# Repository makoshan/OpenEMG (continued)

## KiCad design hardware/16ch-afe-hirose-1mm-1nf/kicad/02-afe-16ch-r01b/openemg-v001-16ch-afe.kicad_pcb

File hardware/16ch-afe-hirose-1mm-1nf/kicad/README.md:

# OpenEMG v0.01（16CH 双板 + 九页原理图）— KiCad 8 原生工程

本目录由同级 [`../OpenEMG_v0.01_DualBoard.epro2`](../OpenEMG_v0.01_DualBoard.epro2)（`OpenEMG_v0.01_双板工程_九页原理图_20261115.epro2`）1:1 转换生成，完整保留双板封装焊盘、过孔、铜线、铺铜区域（`zone`）、可见位号丝印（遵循 `.epru` `Designator.valueVisible`）、`LM1` 散热焊盘双窗钢网分割（`78.2%`），以及全部 9 页原理图与立创 `LCSC` / `MPN` 属性。可直接用 **KiCad 8.0+** 或 **Backplane GPUI** 打开查看与联调。

## 目录结构

| 子目录 | 包含文件 | 对应源工程与说明 |
| :--- | :--- | :--- |
| [`02-afe-16ch-r01b/`](02-afe-16ch-r01b/) | `openemg-v001-16ch-afe.kicad_pro`<br>`openemg-v001-16ch-afe.kicad_pcb`<br>`openemg-v001-16ch-afe.kicad_sch` | **`02 采集板（AFE-16CH，R01b）`**：`43.10 × 36.50 mm` 四角 `R1.80` 4 层板（150 器件 = 146 贴片 + 4 定位孔、2239 段铜线、234 过孔、14 铜皮 + `LM1` 双窗钢网）+ `02.01 / 02.02` 合并原理图 |
| [`01-mainboard-c08b-u9/`](01-mainboard-c08b-u9/) | `openemg-v001-mainboard-u9.kicad_pro`<br>`openemg-v001-mainboard-u9.kicad_pcb`<br>`openemg-v001-mainboard-u9.kicad_sch` | **`01 主控板（C08B-U9，OpenEMG）`**：`43.10 × 36.50 mm` 四角 `R1.80` 6 层板（`STM32L432KB + nRF52840`，128 器件、1114 段铜线、204 过孔、24 铜皮）+ `01.01 ~ 01.07` 合并原理图 |
| [`nine-pages-sch/`](nine-pages-sch/) | `01_01.kicad_sch` ～ `01_07.kicad_sch`<br>`02_01.kicad_sch` ～ `02_02.kicad_sch` | **9 页独立单页 KiCad 原理图**：`01.01` 整机框图、`01.02` 电源树、`01.03–01.07` 主控电路、`02.01` 双 `ADS1298R` 与模拟电源、`02.02` 双 30P 广濑接口与 32 路 `ESD401DPYR` 滤波网络 |

> **投产提示**：打板与 SMT 贴片请直接使用上级目录经人工工程师逐脚审核定版的生产制造包（[`../Gerber_AFE-30P.zip`](../Gerber_AFE-30P.zip)、[`../Gerber_C08B-U9_v0.01.zip`](../Gerber_C08B-U9_v0.01.zip)、[`../jlc_smt_bom.csv`](../jlc_smt_bom.csv)、[`../jlc_smt_cpl.csv`](../jlc_smt_cpl.csv)）。

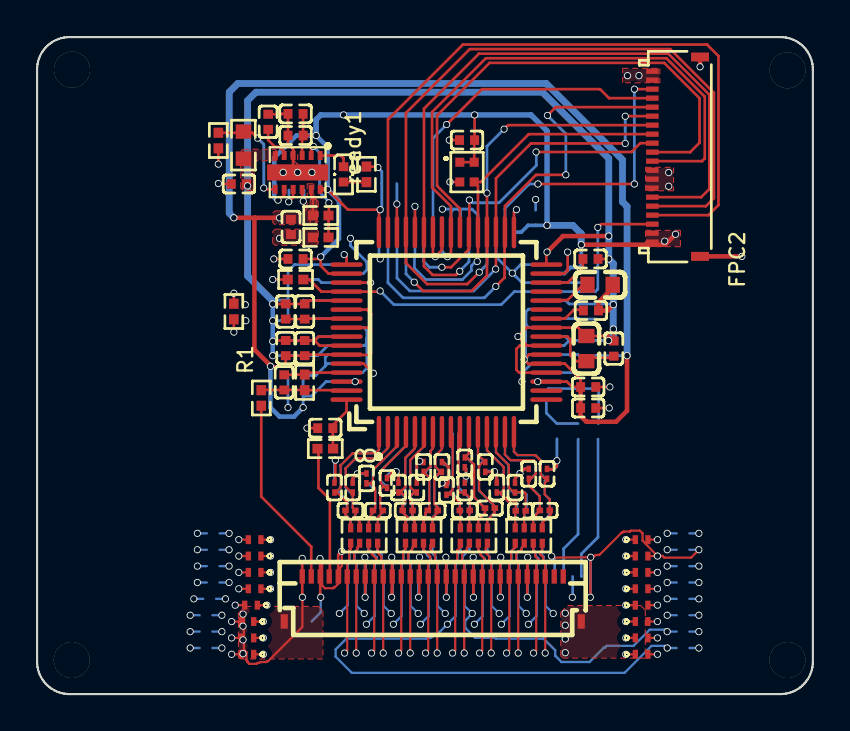
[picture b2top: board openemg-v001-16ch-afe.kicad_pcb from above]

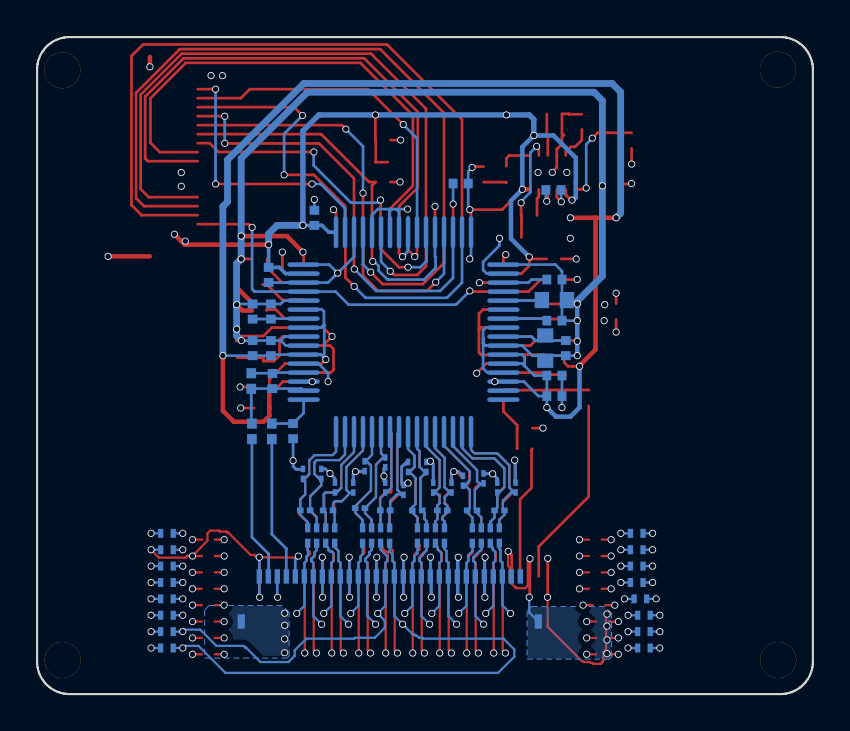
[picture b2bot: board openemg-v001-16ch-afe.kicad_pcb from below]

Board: 4 copper layers, 43.1 x 36.5 mm, 150 parts (66 on the bottom side), 109 nets.

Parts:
C1, C2: 22uF; C0603
C3, C5, C8, C18, C21, C22, C24, C26, C28, C30, C32, C37: 100nF; C0402
C4, C34: 47uF; C0603
C6, C7: 2.2uF; C0402
C9, C11: 10uF; C0402
C10, C12, C13, C15, C16, C19, C20, C23, C25, C27, C29, C31, C33: 1uF; C0402
C14, C17: 10nF; C0402
C55, C57, C58, C59, C60, C61, C62, C63, C64, C65, C66, C67, C68, C69, C70, C71, C93, C94, C95, C96, C97, C98, C99, C100, C101, C102, C103, C104, C105, C106, C107, C108: 470pF; C0201
C72, C73, C74, C75, C76, C77, C78, C79, C109, C110, C111, C112, C113, C114, C115, C116: 1nF; C0201
C123, C124: 100pF; C0402
D101, D102, D103, D104, D105, D106, D107, D108, D109, D110, D111, D112, D113, D114, D115, D116, D117, D118, D119, D120, D121, D122, D123, D124, D125, D126, D127, D128, D129, D130, D131, D132: ESD401DPYR; X1SON-2_L1.0-W0.6-P0.65-BI
FPC1, FPC3: FH34SRJ-30S-0.5SH(50); FFC-SMD_30P-P0.50_FH34SRJ-30S-0.5SH
FPC2: 5034802000; FPC-SMD_5034802000
LM1: LM27762DSSR; WSON-12_L3.0-W2.0-P0.50-BL-EP
R1: 0Ω; R0402
R3, R5: 100kΩ; R0402
R4: 104kΩ; R0603
R6: 107kΩ; R0402
R17, R35, R37: 10kΩ; R0402
R24, R32, R34, R36: 392kΩ; R0402
R_pu1: 10kΩ; R0402
SCREW1, SCREW2, SCREW3, SCREW4: M2螺丝
U1, U2: ADS1298IPAGR; TQFP-64_L10.0-W10.0-P0.50-LS12.0-BL
U3, U4, U5, U6, U7, U8, U9, U10: 15kΩ; RES-ARRAY-SMD_0402-8P-L2.0-W1.0-BL
X1: 2.048MHz; OSC-SMD_4P-L1.6-W1.2-BL
ready1: XL-1005UGC; LED0402-RD_GREEN

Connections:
$1N19: C3.2, C4.2, U1.24
$1N24: C12.1, U1.26
$1N26: C13.1, U1.30
$1N44: C20.2, C21.2, U1.55
$1N303: C16.1, U2.30
$1N305: C15.1, U2.26
$1N315: C5.2, C34.2, U2.24
$1N319: C18.2, C19.2, U2.55
$1N346: C123.1, R35.1, U1.64
$1N349: C124.1, R37.1, U2.64
$1N350: C1.1, U1.28
$1N351: C2.1, U2.28
$1N375: C11.1, LM1.5
$1N383: C10.2, LM1.9
$1N384: C10.1, LM1.10
$1N395: R_pu1.2, ready1.2
+2.5V: C6.1, C24.1, C25.1, C26.1, C27.1, C30.1, C31.1, C32.1, C33.1, LM1.11, R6.2, U1.19, U1.21, U1.22, U1.54, U1.56, U1.59, U1.62, U2.19, U2.21, U2.22, U2.54, U2.56, U2.59, U2.62
+3.3V: C8.2, C9.1, C22.1, C23.1, C28.1, C29.1, C37.2, FPC2.1, FPC2.2, LM1.3, LM1.8, LM1.12, R_pu1.1, U1.48, U1.50, U2.48, U2.50, X1.1, X1.4
-2.5V: C1.2, C2.2, C3.1, C4.1, C5.1, C7.1, C12.2, C13.2, C15.2, C16.2, C18.1, C19.1, C20.1, C21.1, C26.2, C27.2, C32.2, C33.2, C34.1, LM1.6, R4.2, U1.20, U1.23, U1.25, U1.32, U1.53, U1.57, U1.58, U2.20, U2.23, U2.25, U2.32, U2.53, U2.57, U2.58
AGND: C6.2, C7.2, C8.1, C9.2, C11.2, C24.2, C25.2, C30.2, C31.2, C55.1, C57.1, C58.1, C59.1, C60.1, C61.1, C62.1, C63.1, C64.1, C65.1, C66.1, C67.1, C68.1, C69.1, C70.1, C71.1, C93.1, C94.1, C95.1, C96.1, C97.1, C98.1, C99.1, C100.1, C101.1, C102.1, C103.1, C104.1, C105.1, C106.1, C107.1, C108.1, C123.2, C124.2, D101.2, D102.2, D103.2, D104.2, D105.2, D106.2, D107.2, D108.2, D109.2, D110.2, D111.2, D112.2, D113.2, D114.2, D115.2, D116.2, D117.2, D118.2, D119.2, D120.2, D121.2, D122.2, D123.2, D124.2, D125.2, D126.2, D127.2, D128.2, D129.2, D130.2, D131.2, D132.2, FPC1.5, FPC1.8, FPC1.11, FPC1.14, FPC1.17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
BIASINV1: C14.1, R24.1, U1.61
BIASINV12: C17.1, R32.1, U2.61
BIASOUT1: C14.2, R24.2, R34.1, U1.63
BIASOUT12: C17.2, R32.2, R36.1, U2.63
BIAS_DRV1: FPC1.29, R34.2
BIAS_DRV12: FPC3.29, R36.2
CLK: FPC2.13, U1.37, U2.37, X1.3
CLKSEL: FPC2.3, R17.2, U1.52, U2.52
CS#: FPC2.11, U1.39
CS#2: FPC2.17, U2.39
DIN: FPC2.16, U1.34, U2.34
DOUT: FPC2.6, U1.43, U2.43
DRDY2#: FPC2.18, U2.47
DRDY#: FPC2.4, U1.47
EL_CH1_N: D102.1, FPC1.4, U6.2
EL_CH1_P: D101.1, FPC1.3, U6.1
EL_CH2_N: D104.1, FPC1.7, U6.4
EL_CH2_P: D103.1, FPC1.6, U6.3
EL_CH3_N: D106.1, FPC1.10, U5.2
EL_CH3_P: D105.1, FPC1.9, U5.1
EL_CH4_N: D108.1, FPC1.13, U5.4
EL_CH4_P: D107.1, FPC1.12, U5.3
EL_CH5_N: D110.1, FPC1.16, U4.2
EL_CH5_P: D109.1, FPC1.15, U4.1
EL_CH6_N: D112.1, FPC1.19, U4.4
EL_CH6_P: D111.1, FPC1.18, U4.3
EL_CH7_N: D114.1, FPC1.22, U3.2
EL_CH7_P: D113.1, FPC1.21, U3.1
EL_CH8_N: D116.1, FPC1.25, U3.4
EL_CH8_P: D115.1, FPC1.24, U3.3
EL_CH9_N: D118.1, FPC3.4, U10.2
EL_CH9_P: D117.1, FPC3.3, U10.1
EL_CH10_N: D120.1, FPC3.7, U10.4
EL_CH10_P: D119.1, FPC3.6, U10.3
EL_CH11_N: D122.1, FPC3.10, U9.2
EL_CH11_P: D121.1, FPC3.9, U9.1
EL_CH12_N: D124.1, FPC3.13, U9.4
EL_CH12_P: D123.1, FPC3.12, U9.3
EL_CH13_N: D126.1, FPC3.16, U8.2
EL_CH13_P: D125.1, FPC3.15, U8.1
EL_CH14_N: D128.1, FPC3.19, U8.4
EL_CH14_P: D127.1, FPC3.18, U8.3
EL_CH15_N: D130.1, FPC3.22, U7.2
EL_CH15_P: D129.1, FPC3.21, U7.1
EL_CH16_N: D132.1, FPC3.25, U7.4
EL_CH16_P: D131.1, FPC3.24, U7.3
FB: LM1.2, R3.2, R6.1
FB-: LM1.7, R4.1, R5.2
GND: C22.2, C23.2, C28.2, C29.2, C37.1, FPC2.7, FPC2.8, FPC2.9, FPC2.19, FPC2.20, FPC2.21, FPC2.22, R1.2, R17.1, U1.31, U1.33, U1.41, U1.42, U1.44, U1.46, U1.49, U1.51, U2.31, U2.33, U2.41, U2.42, U2.44, U2.46, U2.49, U2.51, X1.2
GPIO3: FPC2.5, U1.45, U2.45
IN1N: C57.2, C72.1, U1.15, U6.7
IN1N2: C94.2, C109.1, U2.15, U10.7
IN1P: C55.2, C72.2, U1.16, U6.8
IN1P2: C93.2, C109.2, U2.16, U10.8
IN2N: C59.2, C73.1, U1.13, U6.5
IN2N2: C96.2, C110.1, U2.13, U10.5
IN2P: C58.2, C73.2, U1.14, U6.6
IN2P2: C95.2, C110.2, U2.14, U10.6
IN3N: C61.2, C74.1, U1.11, U5.7
IN3N2: C98.2, C111.1, U2.11, U9.7
IN3P: C60.2, C74.2, U1.12, U5.8
IN3P2: C97.2, C111.2, U2.12, U9.8
IN4N: C63.2, C75.1, U1.9, U5.5
IN4N2: C100.2, C112.1, U2.9, U9.5
IN4P: C62.2, C75.2, U1.10, U5.6
IN4P2: C99.2, C112.2, U2.10, U9.6
IN5N: C65.2, C76.1, U1.7, U4.7
IN5N2: C102.2, C113.1, U2.7, U8.7
IN5P: C64.2, C76.2, U1.8, U4.8
IN5P2: C101.2, C113.2, U2.8, U8.8
IN6N: C67.2, C77.1, U1.5, U4.5
IN6N2: C104.2, C114.1, U2.5, U8.5
IN6P: C66.2, C77.2, U1.6, U4.6
IN6P2: C103.2, C114.2, U2.6, U8.6
IN7N: C69.2, C78.1, U1.3, U3.7
IN7N2: C106.2, C115.1, U2.3, U7.7
IN7P: C68.2, C78.2, U1.4, U3.8
IN7P2: C105.2, C115.2, U2.4, U7.8
IN8N: C71.2, C79.1, U1.1, U3.5
IN8N2: C108.2, C116.1, U2.1, U7.5
IN8P: C70.2, C79.2, U1.2, U3.6
IN8P2: C107.2, C116.2, U2.2, U7.6
POWERGOOD: LM1.1, ready1.1
PWDN#: FPC2.15, U1.35, U2.35
RESET#: FPC2.14, U1.36, U2.36
SCLK: FPC2.10, U1.40, U2.40
START: FPC2.12, U1.38, U2.38
WCT: FPC1.27, R35.2
WCT2: FPC3.27, R37.2

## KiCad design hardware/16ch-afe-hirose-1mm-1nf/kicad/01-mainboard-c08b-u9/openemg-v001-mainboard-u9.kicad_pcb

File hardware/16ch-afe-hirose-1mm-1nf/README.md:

# 16 通道双板汇总工程与 1.0 mm 广濑双 30 针 1 nF 采集板（`v0.01`）

**2026-11-15 人工工程师设计并逐脚审核通过（ESD32 · 准备下单打样）。** 本目录双板（`01 主控板 C08B-U9` + `02 采集板 AFE-30P`）是当前仓库中**唯一由人工硬件工程师设计、并对照 TI `ADS1298` 手册与 `SBAU171D` 评估板指南逐脚审核通过、准备下单打样的硬件定版**；仓库内其余 2/8/16 通道衍生板、柔性电极软板与 3D 外壳均为 AI 生成且尚未下单。项目仍在早期研制，尚无本版整机台架或佩戴实测。

本目录归档 `OpenEMG v0.01` 双板合并嘉立创 EDA 专业版工程（含 6 层主控板与 4 层 16 通道采集板，共 9 页原理图 + 2 块圆角 `43.10 × 36.50 mm`、`R1.80` PCB），以及与该工程采集板逐位号同步导出的四层单板生产制造包。

| 识别项 | 本目录广濑 `1 nF` 版（`v0.01`） | [讯普 `2.0 mm` `1 nF` 版](../16ch-afe-xunpu-2mm-1nf/) | [广濑 `22 pF` 穿戴版](../16ch-u9-dual30/) |
|---|---|---|---|
| 工程形态 | 双板合并 `.epro2`（`01 主控板` + `02 采集板`） | 采集板独立 `.epro` / `.epro2` | 主控与采集板分立 `.epro2` + 软板 + 外壳 |
| 板框包络 | `43.10 × 36.50 mm`，四角 `R1.80` 圆角 | `43.10 × 36.67 mm`，直角 | `43.10 × 36.50 mm`，四角 `R1.80` 圆角 |
| `FPC1`、`FPC3` 表带座 | 广濑 `FH34SRJ-30S-0.5SH(50)`，`1.0 mm` 超薄上下双触点，`C324727` | 讯普 `FPC-05F-30PH20`，`2.0 mm`，`C2856808` | 广濑 `FH34SRJ-30S-0.5SH(50)`，`1.0 mm`，`C324727` |
| 输入 RC 网络 | `32 × 15 kΩ` + `32 × 470 pF` 对地 + `16 × 1 nF` 跨通道 | `32 × 15 kΩ` + `32 × 470 pF` 对地 + `16 × 1 nF` 跨通道 | `32 × 15 kΩ` + 32 颗共模空贴 DNP + `16 × 22 pF` 跨通道 |
| 负电源反馈 `R4` | `104 kΩ ±0.1%`（0603，`RT0603BRD07104KL`，`C861070`，现货） | `105 kΩ`（0402，`C2984407`） | `105 kΩ ±0.1%`（0402，`C2984407`） |
| 偏置串阻 `R34`、`R36` | `392 kΩ`（0402，`C27007`） | `392 kΩ`（暂选待回签） | `392 kΩ`（0402，`C99199`，配 `100 kΩ/200 kΩ` 保护软板） |

### 在线看图

[九页原理图（矢量 PDF）](views/schematic.pdf) · [主控六层走线](views/mcu-copper.png) · [采集四层走线](views/afe-copper.png) · [双板叠放](views/v001-stack-iso-dark.png) · [结构爆炸图](views/v001-exploded-iso-dark.png)

公开工程沿用 11 月 15 日的 PCB。主控五页按功能标出电源、接口、蓝牙和采样主控。采集部分按 CH1–8、CH9–16 标注芯片和滤波器，输入保护管 D101–D132 按通道顺序排列，使用 ESD401 的双向保护符号。

九页 PDF 由整机框图、电源树、主控电路五页和[从公开工程导出的采集板两页](views/afe-schematic.pdf)合并。D101–D132 分布在两面，分别保护 32 根输入线。走线图使用本目录两个 Gerber 包，按顶层、内层、底层排列，底层保持板顶视角。装配图使用相同 Gerber 的板框、阻焊和丝印，搭配 U9 壳体 CAD，按 0.8 mm 裸板展示。

### 工程与制造文件

2026-11-15 离体台架打样版已同步。两块 PCB 各删除四处安装孔的顶层圆圈和斜线，孔位、铜层、钢网和钻孔文件与上一版一致。打样以以下 Gerber、BOM 和坐标为准，上方装配渲染为改丝印前的示意。

[双板合并嘉立创工程 `.epro2`](OpenEMG_v0.01_DualBoard.epro2) · [KiCad 8 原生工程（双板 PCB + 九页原理图）](kicad/) · [采集板单板 Gerber（含钻孔与 `LM1` 双窗钢网）](Gerber_AFE-30P.zip) · [采集板贴片 BOM](jlc_smt_bom.csv) · [采集板贴片坐标 CPL](jlc_smt_cpl.csv)

- **采集板贴片清单**：整板共 **24 种料、146 个贴片位号**（顶面 80 个、底面 66 个，已剔除 4 个非贴片定位孔 `SCREW1–SCREW4`）；上传 `jlc_smt_cpl.csv` 时保持嘉立创平台默认的 **「AD,99SE,Allegro,PADS(宏)等其他」** 选项（切勿改选「嘉立创EDA」），并在贴片预览页核对 `U1/U2/FPC1–FPC3` 第 1 脚朝向。Gerber、BOM、CPL 与底面装配图成套同步，不可与直角框或 `0402 R4` 的历史文件混用。
- **配套主控板制造包**：双板工程内的 `01 主控板` 与 [`../16ch-u9-dual30/fab-mcu-u9/`](../16ch-u9-dual30/fab-mcu-u9/) 铜皮走线及 110 颗贴片位号一致（主控贴片需排除测试点、焊盘电池座 `J401` 及默认禁贴跨接件 `JP701 / R7 / R213`，本版使用[主控贴片 BOM](mainboard_bom.csv) 和[双面坐标](mainboard_cpl.csv)，本次主控打样使用[评审后主控单板 Gerber](Gerber_C08B-U9_v0.01.zip)；注：`.epro2` 源内 `J401` 原理图符号保留第 3 空置 NTC 引脚且机械定位孔勾有加入 BOM，切勿从 `.epro2` 直接一键导出 BOM/钢网投产）。

### 采集板打样与安全边界须知

- 按定版打样包选择盘中孔树脂塞孔、电镀盖帽。LM1 顶面散热焊盘的钢网已分成双窗，使用本目录 Gerber。
- 离体台架首板按 1.6 mm 板厚；U9 外壳渲染按 0.8 mm 裸板展示，装壳与排线仍需试装。
- 两颗 `ADS1298` 的 `Pin 60 (RLDREF)` 接 `AGND`、`Pin 62 (RLDIN)` 接 `+2.5 V`、`Pin 17/18 (TESTP/TESTN)` 独立悬空。[`firmware/c08b-bringup`](../../firmware/c08b-bringup/) 与 [`firmware/c08b-stream`](../../firmware/c08b-stream/) 已据此完成寄存器与网表对齐（`TST1` 下双片均置 `CONFIG2=0x10`，`CONFIG3` 强制 `(val & 0x38)==0` 禁置 `VREF_4V / RLD_MEAS / RLDREF_INT` 且禁设 `MUX=0x02`）。偏置回路、通道底噪、丢帧与佩戴安全尚待首板实测验证。[安全说明](../../SAFETY.md)

### 双面贴片方向

[顶面贴片极性图](assembly-top.png) · [底面贴片极性图](assembly-bottom.png)。红点标出第 1 脚，角度对应同版 CPL。底面图按翻到板背后的方向显示。

### 配套表带软板（A5＋B1）与 25 mm R3 外壳套件（已下单 · 待实物试装）

- **[双层表带柔性电极软板 `strap-fpc-a5b1/`](strap-fpc-a5b1/)**：适配本目录双 30 针采集板（`FPC1`、`FPC3`），采用盒底 **A 板 5 根 + B 板 `U10`（`BIAS_2`）折回补第 6 根**方案，含嘉立创 EDA 专业版源工程 [`OpenEMG_v0.01_Strap_FPC_A5B1.epro2`](strap-fpc-a5b1/OpenEMG_v0.01_Strap_FPC_A5B1.epro2)、平铺 Gerber（含 `.GBSL`/`.GTSL` `0.20 mm` PI 补强层）与顶面 17 颗 `0402` 限流电阻 BOM/CPL。
- **[25 mm 表带与 R3 外壳结构套件 `enclosure-25mm-r3/`](enclosure-25mm-r3/)**：含替换了 **`15.90 × 15.00 mm` 修订六孔底盖**的 78 实体整机模型 [`assembly.step`](enclosure-25mm-r3/assembly.step)、4 件树脂外壳（`cap` / `tray` / `cover` / `side_button`）、2 件 `TPU` 保护表带（`north_backing` / `south_backing`）的独立 `.step` 与 `.stl`，以及 `0.8 mm` 片材电极内衬裁切图 [`liner-0.8mm-cut.dxf`](enclosure-25mm-r3/liner-0.8mm-cut.dxf)。

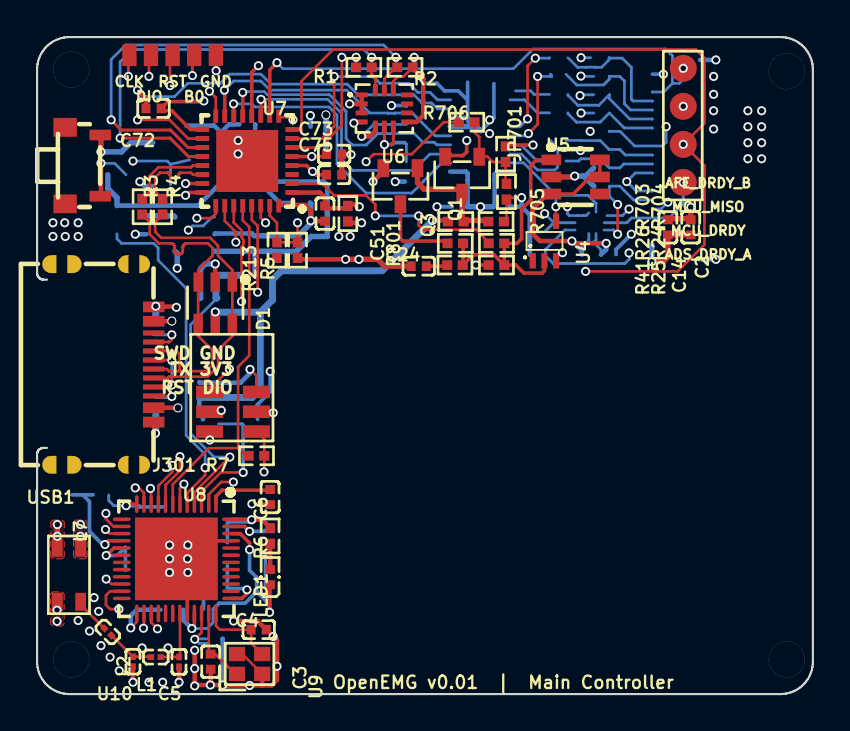
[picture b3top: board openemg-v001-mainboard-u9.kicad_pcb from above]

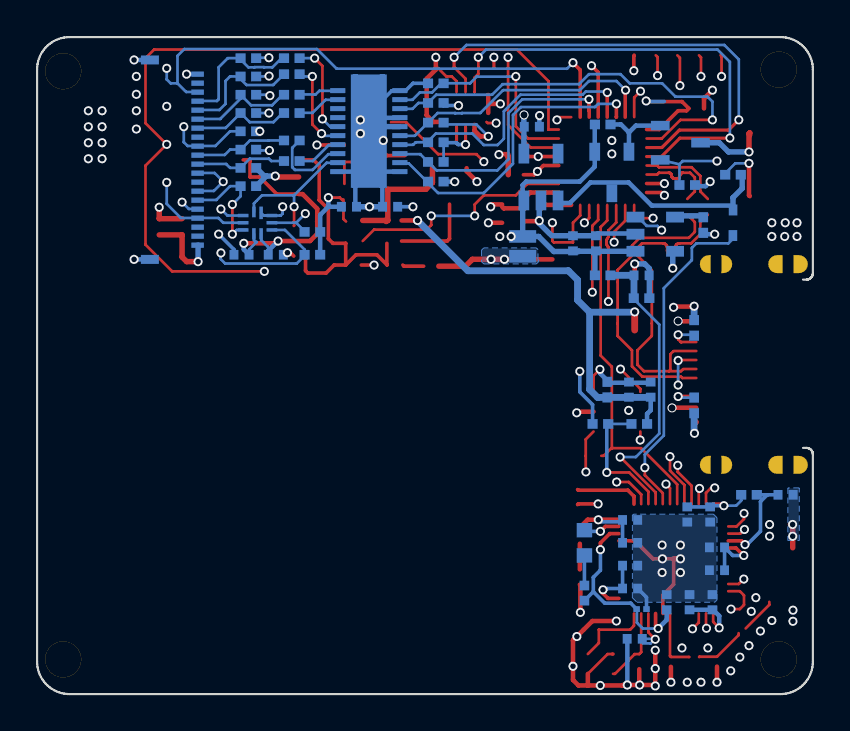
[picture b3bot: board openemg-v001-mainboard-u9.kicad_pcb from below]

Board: 6 copper layers, 43.1 x 36.5 mm, 128 parts (69 on the bottom side), 81 nets.

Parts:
BOOT0: GND; TP_1p5
C2, C6, C12, C13, C26, C27, C28, C29, C30, C31, C39, C40, C61, C63, C64, C65, C72, C73, C75: 100nF; C0402
C3, C4: 12pF; C0402
C5: 1pF; C0201
C7: 100pF; C0402
C8, C10, C24, C32, C43, C51: 1uF; C0402
C9: 47nF; C0201
C11, C34, C52, C53: 2.2uF; C0402
C14: 10uF; C0402
D1: USBLC6-2SC6; SOT-23-6_L2.9-W1.6-P0.95-LS2.8-BL
D2: BAT54C; SOT-23-3_L2.9-W1.3-P1.90-LS2.8-BR
D4: RB521S-30; SOD-523F_L1.2-W0.8-LS1.7-RD
FPC1: 5034802000; FPC-SMD_5034802000
J301: SWD + UART pads; J301
J401: BAT pads (NTC pad unused); J401
JP701: 10K; R0402
L1: 4.7nH; L0201
L2: 2.2nH; L0201
L3: 10uH; L0603
L4: 15nH; L0402
L7: 2450AT18D0100002E; ANT-SMD_4P-L3.2-W1.6
LED1: XL-1005UGC; LED0402-RD_GREEN
NRST: GND; TP_1p5
Q1, Q3: AO3400A; SOT-23-3_L2.9-W1.3-P1.90-LS2.4-BR
Q2: AO3401A; SOT-23_L2.9-W1.3-P1.90-LS2.4-BR
R1, R2, R41: 4.7kΩ; R0402
R3, R4, R810, R811, R812, R813, R814, R815: 33Ω; R0402
R5, R13, R14, R15, R35, R36, R37, R39, R42, R703: 10kΩ; R0402
R6: 100Ω; R0402
R7, R213: 10K; R0402
R8, R9, R25, R34, R701, R702, R704, R705, R827: 100kΩ; R0402
R10: 68kΩ; R0402
R11, R12, R44, R706: 1MΩ; R0402
R16, R17: 5.1kΩ; R0402
R24, R820, R821, R822, R823, R824, R825, R826: 47kΩ; R0402
R26: 0Ω; R0402
R202: 20kΩ; R0402
R801: 470mΩ; R0402
SCREW1, SCREW2, SCREW3, SCREW4: M2螺丝
SWCLK: GND; TP_1p5
SWDIO: GND; TP_1p5
TP701: ADS_DRDY_A; TP_1p5
TP702: XIAO_DRDY; TP_1p5
TP703: ADS_DRDY_B; TP_1p5
TP704: XIAO_MISO; TP_1p5
TP705: GND; TP_1p5
U1: SH-1806SA-A3DW-04; SW-SMD_SH-1806SA-A3DW-04-1
U4: SN74AUP1T14DCKR; SC-70-5_L2.0-W1.3-P0.65-LS2.1-BL
U5: TPS3808G33DBVR; SOT-23-6_L2.9-W1.6-P0.95-LS2.8-BR
U6: LSM6DS3TR-C; LGA-14_L3.0-W2.5-P0.50-TL
U7: STM32L432KCU6; UFQFPN-32_L5.0-W5.0-P0.50-TL-EP3.5
U8: NRF52840-QFAA-F-R; QFN-48_L6.0-W6.0-P0.40-TL-EP4.6
U9: 32MHz; CRYSTAL-SMD_4P-L2.0-W1.6-BL
U10: 1.2pF; C0201
U16: SN74AXC8T245RHLR; VQFN-24_L5.6-W3.6-P0.50-BL-EP
U17: LTC4054ES5-4.2#TRPBF; SOT-23-5_L2.9-W1.6-P0.95-LS2.8-BL
U18: TLV75533PDBVR; SOT-23-5_L3.0-W1.7-P0.95-LS2.8-BR
U19: SN74AXC2T245RSWR; UQFN-10_L1.8-W1.4-P0.40-TL
USB1: GT-USB-7014D; USB-C-SMD_GT-USB-7014D

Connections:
3V3: C26.2, C27.2, C28.2, C29.2, C30.2, C32.2, C34.2, C39.2, C40.2, C51.2, C52.2, C53.2, C61.2, C63.2, C64.2, C65.2, C72.2, C73.2, J301.2, JP701.2, R1.2, R2.2, R6.1, R13.2, R14.2, R15.2, R42.2, R801.1, U4.5, U5.3, U5.5, U5.6, U6.5, U6.8, U6.12, U7.1, U7.5, U7.17, U8.12, U8.17, U8.25, U8.37, U8.48, U16.1, U16.2, U16.23, U16.24, U18.5, U19.6, U19.7
3V3_AFE: C2.2, C14.2, FPC1.19, FPC1.20, R801.2, R820.2, R821.2
ADS_CS_A: R810.1, U16.21
ADS_CS_B: R813.1, U16.18
ADS_DRDY_A: FPC1.17, TP701.1, U19.4
ADS_PWDN: R815.1, U16.14
ADS_RESET: R814.1, U16.15
AFE_CS_A: FPC1.10, R810.2, R820.1
AFE_CS_B: FPC1.4, R813.2, R821.1
AFE_DIN: FPC1.5, R812.2, R826.1
AFE_DRDY_B: FPC1.3, TP703.1, U7.10
AFE_GPIO3: FPC1.16, U7.6
AFE_PWDN: FPC1.6, R815.2, R823.1
AFE_RESET: FPC1.7, R814.2, R822.1
AFE_SCLK: FPC1.11, R811.2, R825.1
AFE_START: FPC1.9, R824.1, U7.9
ANA_EN: R24.1, U7.2
ANT_FEED: L2.2, L7.1
BENCH_EN: JP701.1, Q1.1, R705.2, R706.1
BUTTON_N: D2.2, R14.1, U8.14
CC1: R16.2, USB1.A5
CC2: R17.2, USB1.B5
CHG_PROG: R202.2, U17.5
CHRG_N: U8.11, U17.1
DIN_B: R812.1, U16.19
DOUT_B: FPC1.15, R827.1, U19.5
EN_RC: C24.2, R41.2
GND: C2.1, C3.1, C4.1, C5.1, C6.1, C7.1, C8.1, C9.1, C10.1, C11.1, C12.1, C13.1, C14.1, C24.1, C26.1, C27.1, C28.1, C29.1, C30.1, C31.1, C32.1, C34.1, C39.1, C40.1, C43.1, C51.1, C52.1, C53.1, C61.1, C63.1, C64.1, C65.1, C72.1, C73.1, C75.1, D1.2, FPC1.1, FPC1.12, FPC1.14, FPC1.21, FPC1.22, J301.1, J401.2, L7.2, L7.3, L7.4, Q1.2, Q3.2, R5.1, R8.1, R9.1, R11.1, R16.1, R17.1, R25.1, R35.2, R36.2, R37.2, R39.2, R44.1, R202.1, R701.1, R702.2, R704.1, R705.1, R822.2, R823.2, R824.2, R825.2, R826.2, R827.2, TP705.1, U1.1, U4.3, U5.2, U6.1, U6.2, U6.3, U6.6, U6.7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
ILK_D: Q3.3, R26.1
ILK_GATE: Q1.3, Q3.1, R703.1, R704.2
IMU_INT1: U6.4, U7.30
IMU_SCL: R2.1, U6.13, U7.19
IMU_SDA: R1.1, U6.14, U7.20
LED_A: LED1.2, R6.2
LINK_CS: U7.25, U8.10
LINK_MISO: U7.27, U8.8
LINK_MOSI: R7.1, U7.28, U8.7
LINK_RDY: U7.29, U8.6
LINK_SCK: U7.26, U8.9
L_BOOT0: BOOT0.1, R5.2, R213.1, U7.31
L_NRST: C75.2, NRST.1, U7.4
L_SWCLK: SWCLK.1, U7.24
L_SWDIO: SWDIO.1, U7.23
MCU_BENCH_EN: R706.2, U8.2
MCU_CS_B: R42.1, U7.15, U16.6
MCU_DCC: L3.2, U8.47
MCU_DCC_L: L3.1, L4.2
MCU_DEC1: C6.2, U8.1
MCU_DEC3: C7.2, U8.34
MCU_DEC4_6: C8.2, C9.2, L4.1, U8.33, U8.46
MCU_DM: R3.2, U7.21
MCU_DP: R4.2, U7.22
MCU_LED: LED1.1, U8.22
MCU_RST_N: C13.2, J301.6, R15.1, U8.16
MCU_SWDCLK: J301.4, U8.27
MCU_SWDIO: J301.3, R7.2, U8.26
MCU_TX: J301.5, U8.23
MCU_XC1: C3.2, U8.35, U9.1
MCU_XC2: C4.2, U8.36, U9.3
OE_N: U4.4, U8.15, U16.22, U19.2
PWR_EN: D4.1, Q2.3, R44.2, U18.3
PWR_G: D2.1, Q2.1, R34.1
PWR_HOLD: D4.2, U8.5
RF_ANT: C5.2, L1.1, U8.31
RF_MATCH: L1.2, L2.1, U10.2
SCLK_B: R811.1, U16.20
SW_N: D2.3, U1.2
U7_EN: R24.2, R25.2, R26.2, R41.1, U4.2, U5.1
USB_DM: D1.3, D1.4, R3.1, USB1.A7, USB1.B7
USB_DP: D1.1, D1.6, R4.1, USB1.A6, USB1.B6
VBAT: C31.2, C43.2, J401.1, Q2.2, R12.2, R34.2, U17.3, U18.1
VBAT_SENSE: C12.2, R11.2, R12.1, U8.4
VBUS: C10.2, C11.2, D1.5, R8.2, R10.2, R703.2, U17.4, USB1.A4B9, USB1.B4A9
VBUS_SENSE: R9.2, R10.1, U8.3
XIAO_CS: R13.1, U7.14, U16.3
XIAO_DRDY: R701.2, TP702.1, U7.8, U19.9
XIAO_MISO: R702.1, TP704.1, U7.12, U19.8
XIAO_MOSI: R36.1, U7.13, U16.5
XIAO_PWDN: R39.1, U7.7, U16.10
XIAO_RESET: R37.1, U7.18, U16.9
XIAO_SCLK: R35.1, U7.11, U16.4

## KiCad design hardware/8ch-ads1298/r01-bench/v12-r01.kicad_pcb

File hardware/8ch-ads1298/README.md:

# 8 通道 ADS1298 硬件模块（`8ch-ads1298`）

| 三档叠板爆炸对照（中塔为 8ch 纯单面 `D20-8CH` + 外扣底盖 `Cap D2`） | 单片 4 层软板 `D2-8CH`、短版 TPU 定位层与 `F04` 连续背开口表带 |
|---|---|
|  |  |

> *上图为三维光追设计预览，非实物照片，不代表制造或人体佩戴验收通过。*

本目录同时提供纯单面专属 8 通道穿戴叠板、双面通用板单面贴片子集、离体台架开发板及配套柔性表带结构：

1. **`afe-d20-8ch/` 与 `afe-d20n-8ch/`（`43.1×36.5 mm` 纯单面专属 8 通道采集板 · 推荐打样）**
   - 正面 76 颗贴片件，背面 **0 器件、`B.Paste = 0`、`B.Mask = 0`**（100% 绿油绝缘铜皮直接贴合 `302025` 锂电池，免双面贴片翻面费）。
   - **`afe-d20-8ch/`（圆孔版，配螺丝壳 `R12` + 主控 `R4U6`）**：含自包含 KiCad 10 PCB、满载整板 `afe-d20-8ch-3d.step`、**11 页主控+采集全套原理图 [`afe-d20-8ch/views/schematic.pdf`](afe-d20-8ch/views/schematic.pdf)**、**6 页采集板原理图 [`afe-d20-8ch/views/afe-schematic.pdf`](afe-d20-8ch/views/afe-schematic.pdf)**、**34P/20P 逐针核对与验收表 [`afe-d20-8ch/PINOUT-AND-REVIEW.md`](afe-d20-8ch/PINOUT-AND-REVIEW.md)**（含 [`pinout-34p-20p.csv`](afe-d20-8ch/pinout-34p-20p.csv) 与[贴肤触点/排线朝向图](afe-d20-8ch/views/d20-8ch-wiring-orientation.svg)）、`schematics-8ch/`（306 脚逐脚对板）、`fab/` 拼板 Gerber 与 `jlc-eda/` 两份嘉立创工程（11 页全套与 6 页单板）。
   - **`afe-d20n-8ch/`（四角缺口版，配无螺丝壳 `R13` + 主控 `R4U6N`）**：BOM/CPL 与圆孔版逐字节一致，含四角缺口 KiCad 10 PCB、满载整板 `afe-d20n-8ch-3d.step`、`fab/` 拼板 Gerber 与 `jlc-eda/` 两份嘉立创工程（单板 + 含 `R4U6N` 与 `D2-8CH` 软板的全套汇总）。
2. **`strap-fpc-d2-8ch/`（8 通道单片 4 层柔性表带软板 `D2-8CH`）**
   - 单片直插 `V4_FPC1` 34P 座，覆盖胶囊底 2 路 + 2 辅助（双 `200 kΩ` 独立保护串阻，零悬空贴肤金属）与表带 6 路（北 2 路 + 南 4 路），胶囊背面带 6 窗 `0.20 mm` PI 垫片直接复用现成外壳底盖（`fit_3d_check.py` 实测 `0.0 mm³` 零干涉）；含自包含 KiCad 10 工程、`check.py` 20 道门自检、37 实体满载 `strap-d2-8ch-3d.step`、`fab/` 嘉立创 FPC+SMT 直传包（`strap-d2-8ch-gerber.zip` `7ed551d4`，含 `0.10/0.20 mm` 分厚补强层、全基础库 BOM/CPL 与 `.d356` 电测网表）、`jlc-eda/C08B-表带软板-D2-8CH单片.epro2` 及专属短版表带 TPU 电极层 `tpu-layer-d2-8ch/`（北 `26.2×16.2` / 南 `26.2×32.2 mm` STEP/STL、X2D 切片包 `6189e957` 与 1:1 A4 装配裁胶纸样 `5f69d2c3`）。
3. **`stacked-d20-8ch/`（`16ch D20` 共板单面贴片 BOM/CPL 兼容包）**
   - 若手头已有 16 通道 `D20` 裸板，可直接使用本目录的单面 BOM/CPL 仅贴正面 76 颗元件，随附单面贴片构型三维模型 **`c08b-afe-d20-8ch-single-3d.step`** 与校验脚本 `verify_8ch_dnp.py`。
4. **`r01-bench/`（`65.0×60.0 mm` 离体杜邦线台架开发板 `V12-R01` · 已实板验证）**
   - 含 12 页原生 KiCad 原理图、自包含封装库、四层 `1.6 mm` PCB、满载器件整板三维模型 **`v12-r01-3d.step`**、分组 BOM/CPL、`F05` 固件（硬件锁默认关闭）与离体台架验收表 `BENCH-ACCEPTANCE.md`。
5. **`f04-strap-fpc/` 与 `f04-openback-tpu/`（另一路 8 通道弹片软板与背开口一体 TPU 表带套件）**
   - `f04-strap-fpc/`：原生 KiCad 10 工程、自包含几何原语与整板 `fpc-f04-3d.step`。
   - `f04-openback-tpu/`：自包含 `build123d` 参数化源码 `build.py`、单排壳 `shell.step`/`shell-print.stl`、9 排连续内衬 `liner.step`/`liner-print.stl` 与装配总成 `assembled.step`。
6. **`jlc-eda/`**：收录 `F04-八通道软板-原理图+PCB.epro2`；8ch 叠板主机与 `D2-8CH` 软板嘉立创工程分别见 `afe-d20-8ch/jlc-eda/`、`afe-d20n-8ch/jlc-eda/` 与 `strap-fpc-d2-8ch/jlc-eda/`。

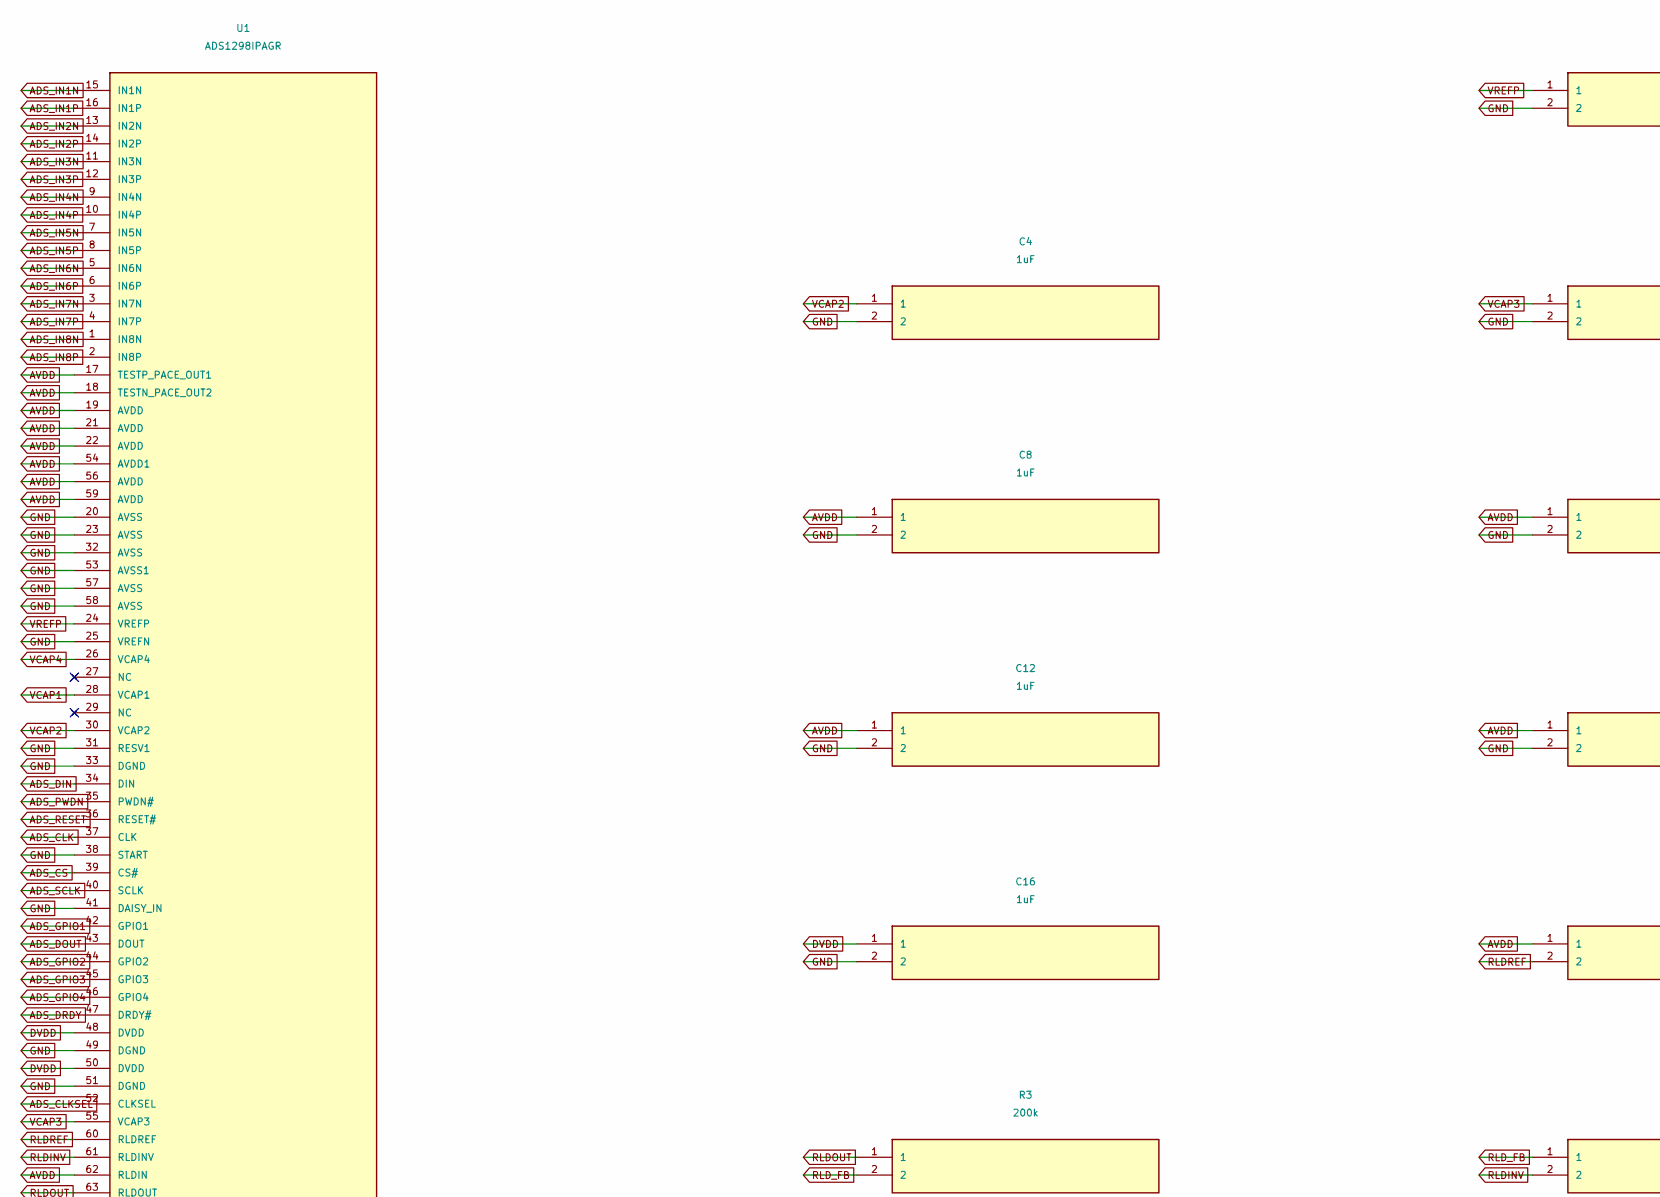
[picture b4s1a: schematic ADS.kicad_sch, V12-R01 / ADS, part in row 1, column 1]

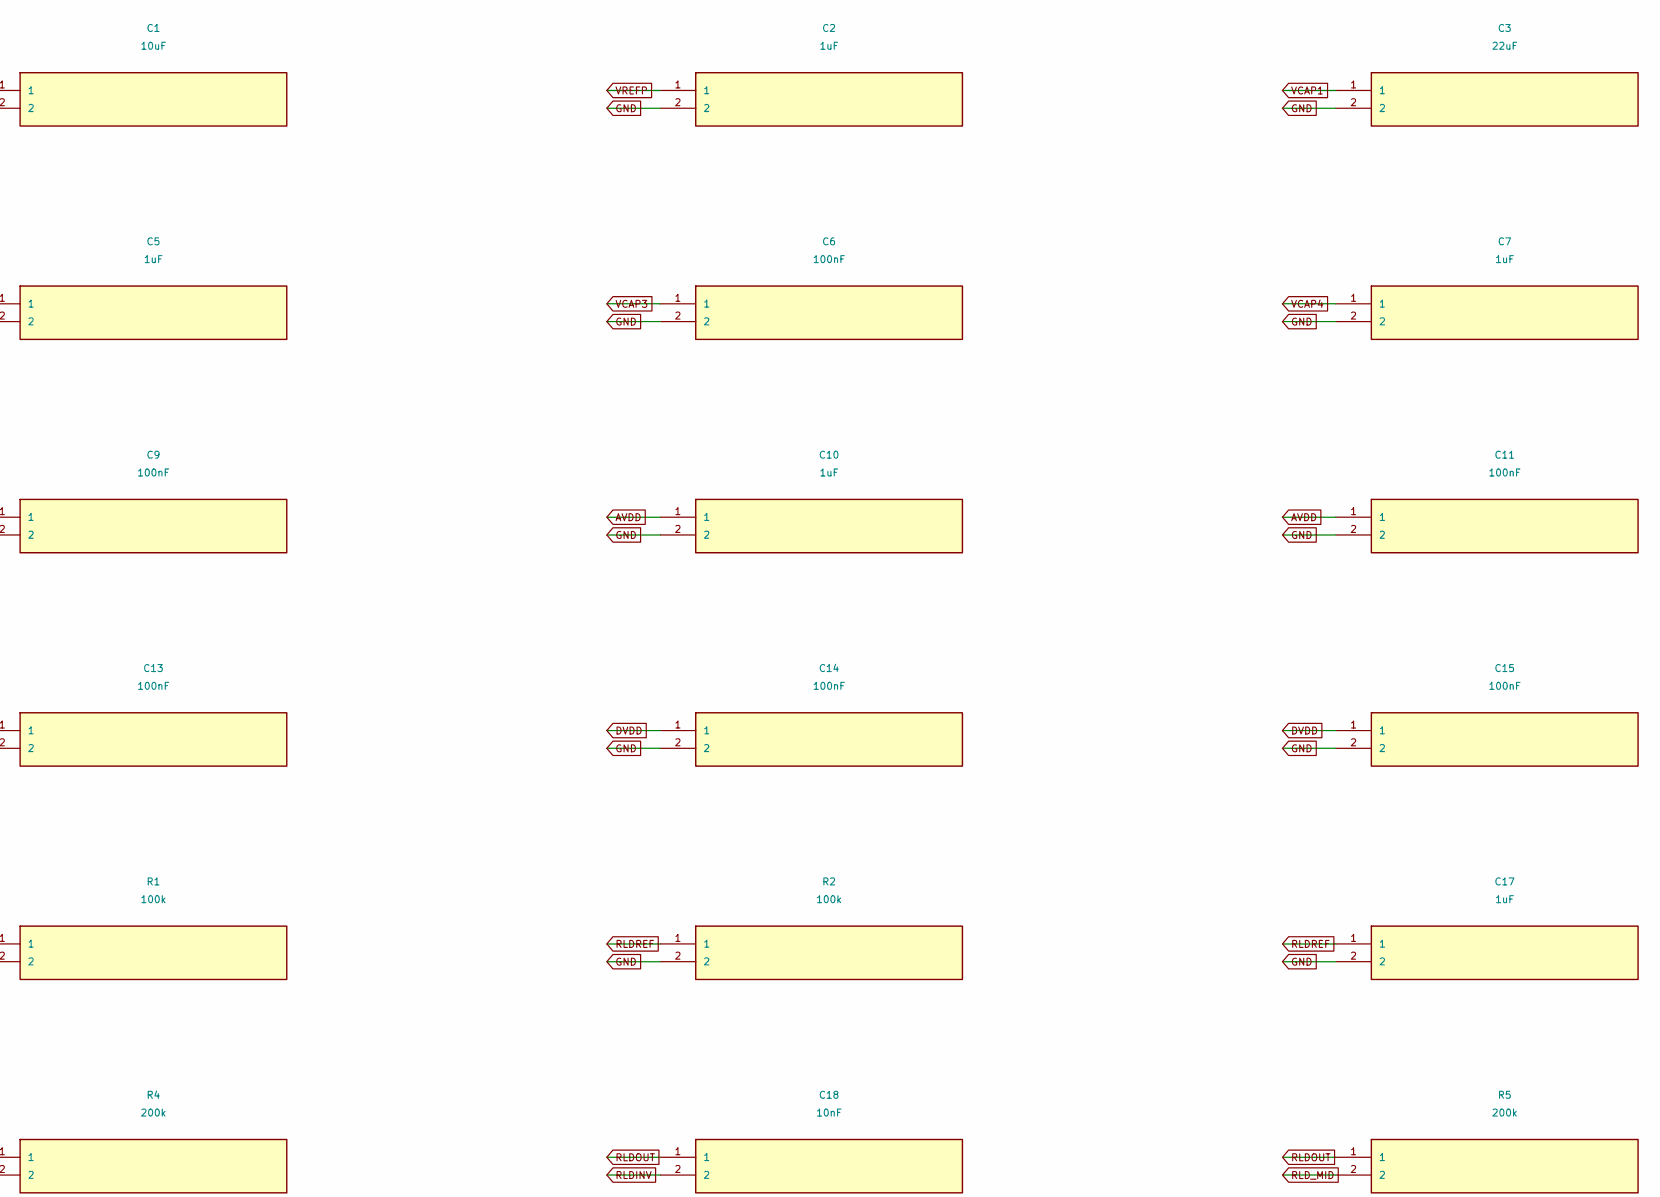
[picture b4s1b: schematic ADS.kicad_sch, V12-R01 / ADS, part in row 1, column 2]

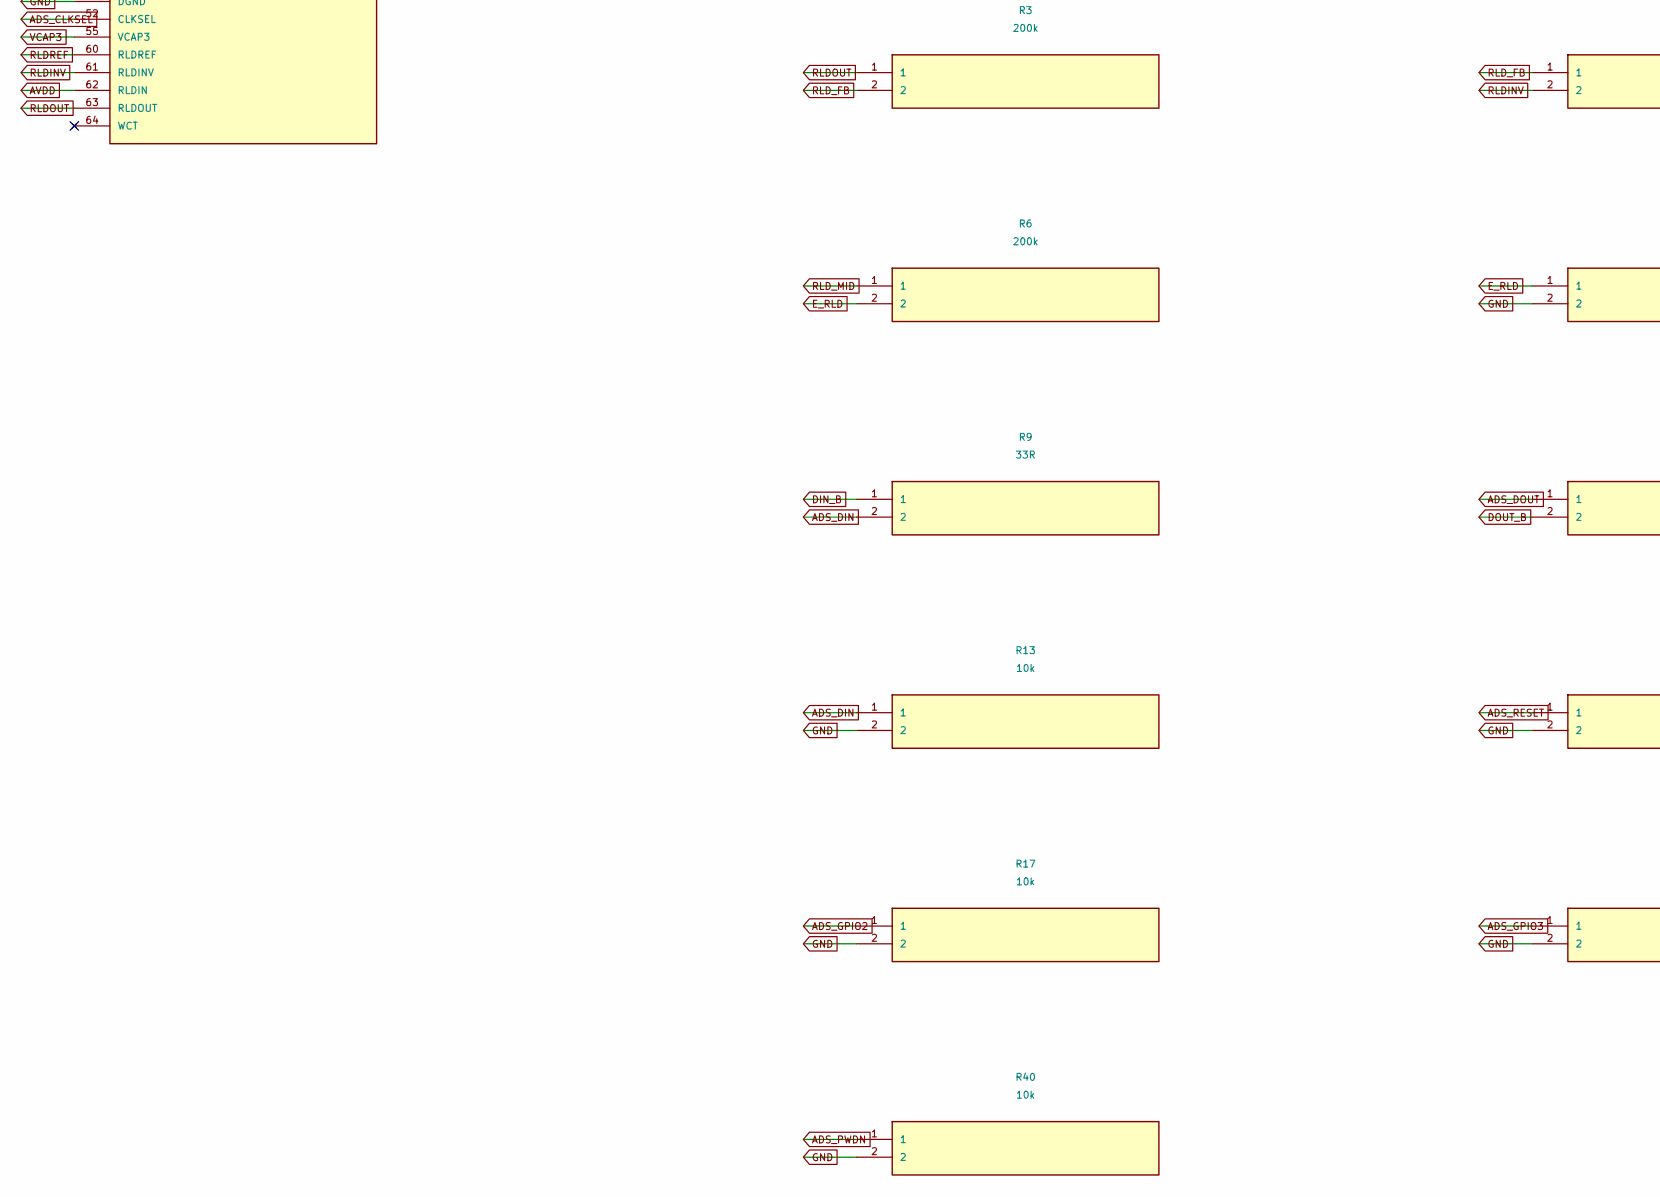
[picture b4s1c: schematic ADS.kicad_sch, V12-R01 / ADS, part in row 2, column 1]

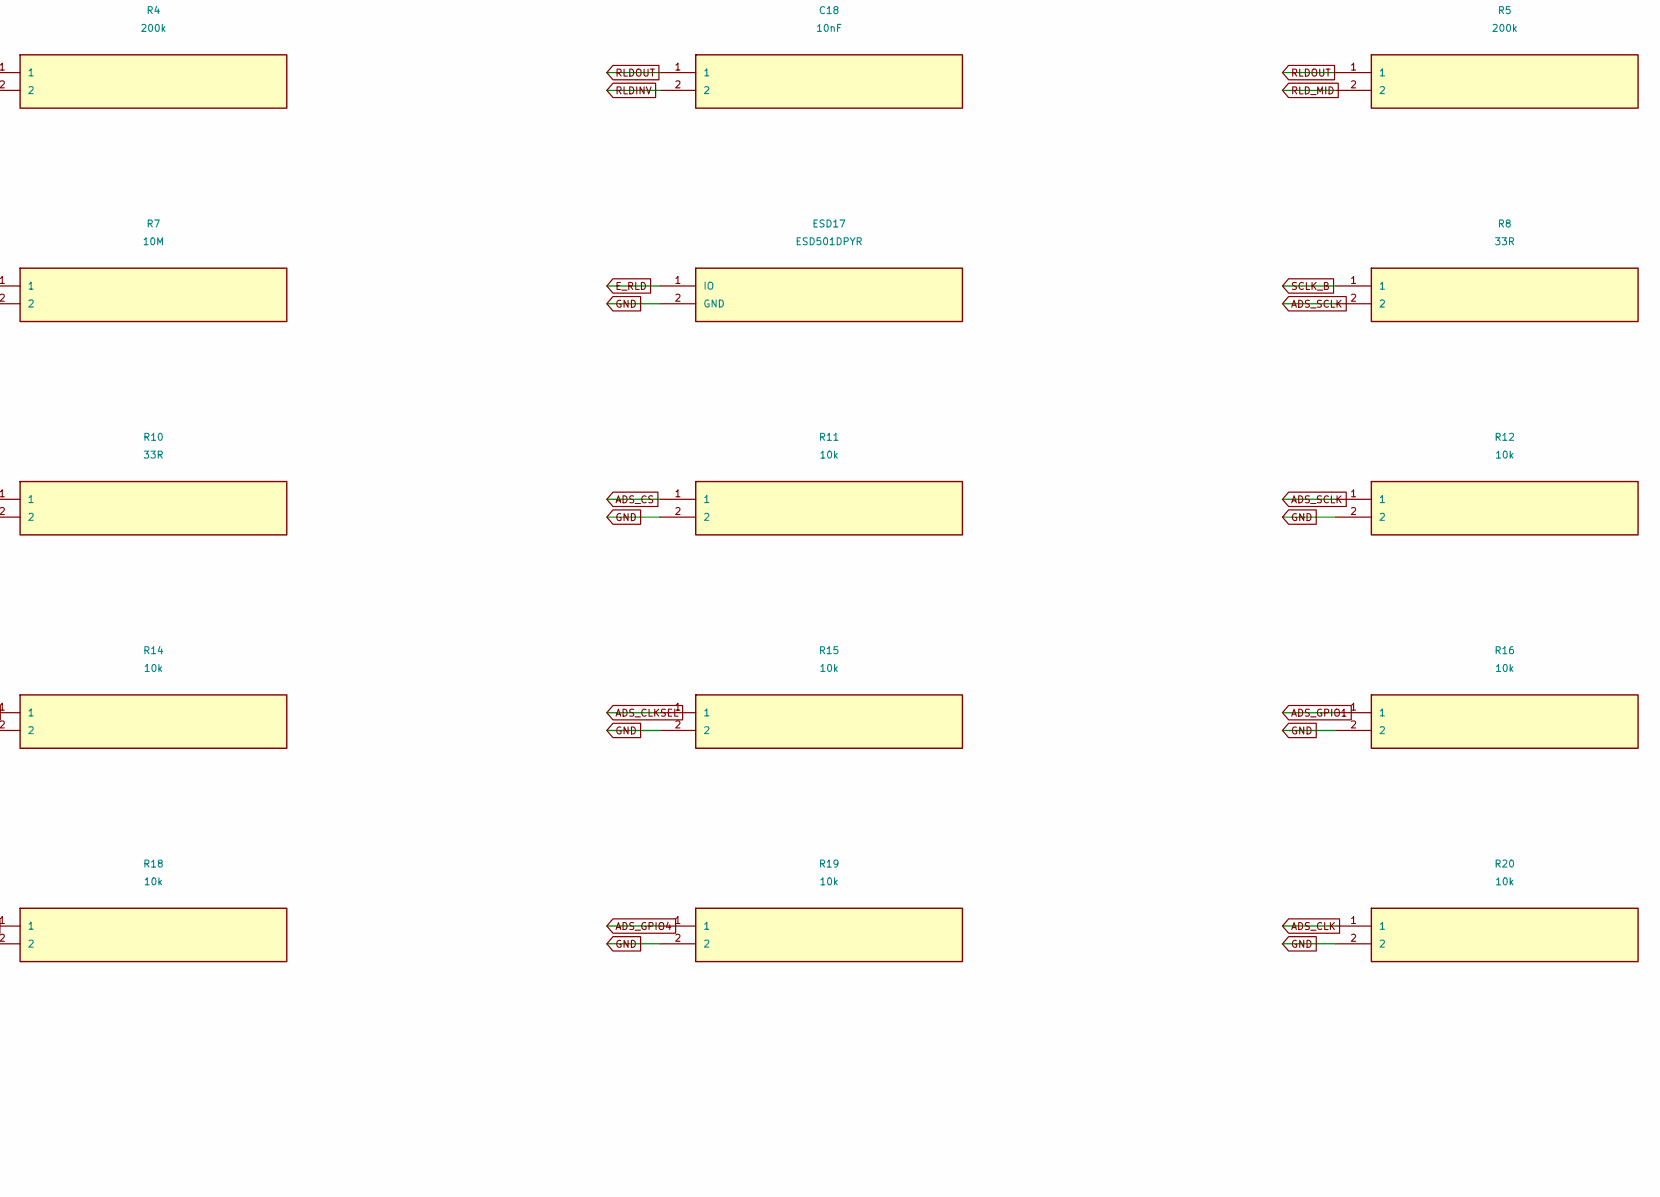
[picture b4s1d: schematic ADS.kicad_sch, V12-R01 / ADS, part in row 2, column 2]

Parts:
C1: 10uF; C_0603_1608Metric
C2, C4, C5, C7, C8, C10, C12, C16, C17: 1uF; C_0402_1005Metric
C3: 22uF; C_0603_1608Metric
C6, C9, C11, C13, C14, C15: 100nF; C_0402_1005Metric
C18: 10nF; C_0402_1005Metric
ESD17: ESD501DPYR; Texas_DPY0002A_0.6x1mm_P0.65mm
R1, R2: 100k; R_0402_1005Metric
R3, R4, R5, R6: 200k; R_0402_1005Metric
R7: 10M; R_0402_1005Metric
R8, R9, R10: 33R; R_0402_1005Metric
R11, R12, R13, R14, R15, R16, R17, R18, R19, R20, R40: 10k; R_0402_1005Metric
U1: ADS1298IPAGR; TQFP-64_10x10mm_P0.5mm

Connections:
ADS_CLK: R20.1, U1.37 (CLK)
ADS_CLKSEL: R15.1, U1.52 (CLKSEL); also elsewhere on the board
ADS_CS: R11.1, U1.39 (CS#); also elsewhere on the board
ADS_DIN: R9.2, R13.1, U1.34 (DIN)
ADS_DOUT: R10.1, U1.43 (DOUT)
ADS_DRDY: U1.47 (DRDY#); also elsewhere on the board
ADS_GPIO1: R16.1, U1.42 (GPIO1)
ADS_GPIO2: R17.1, U1.44 (GPIO2)
ADS_GPIO3: R18.1, U1.45 (GPIO3)
ADS_GPIO4: R19.1, U1.46 (GPIO4)
ADS_IN1N: U1.15 (IN1N); also elsewhere on the board
ADS_IN1P: U1.16 (IN1P); also elsewhere on the board
ADS_IN2N: U1.13 (IN2N); also elsewhere on the board
ADS_IN2P: U1.14 (IN2P); also elsewhere on the board
ADS_IN3N: U1.11 (IN3N); also elsewhere on the board
ADS_IN3P: U1.12 (IN3P); also elsewhere on the board
ADS_IN4N: U1.9 (IN4N); also elsewhere on the board
ADS_IN4P: U1.10 (IN4P); also elsewhere on the board
ADS_IN5N: U1.7 (IN5N); also elsewhere on the board
ADS_IN5P: U1.8 (IN5P); also elsewhere on the board
ADS_IN6N: U1.5 (IN6N); also elsewhere on the board
ADS_IN6P: U1.6 (IN6P); also elsewhere on the board
ADS_IN7N: U1.3 (IN7N); also elsewhere on the board
ADS_IN7P: U1.4 (IN7P); also elsewhere on the board
ADS_IN8N: U1.1 (IN8N); also elsewhere on the board
ADS_IN8P: U1.2 (IN8P); also elsewhere on the board
ADS_PWDN: R40.1, U1.35 (PWDN#); also elsewhere on the board
ADS_RESET: R14.1, U1.36 (RESET#); also elsewhere on the board
ADS_SCLK: R8.2, R12.1, U1.40 (SCLK)
AVDD: C8.1, C9.1, C10.1, C11.1, C12.1, C13.1, R1.1, U1.17 (TESTP_PACE_OUT1), U1.18 (TESTN_PACE_OUT2), U1.19 (AVDD), U1.21 (AVDD), U1.22 (AVDD), U1.54 (AVDD1), U1.56 (AVDD), U1.59 (AVDD), U1.62 (RLDIN); also elsewhere on the board
DIN_B: R9.1; also elsewhere on the board
DOUT_B: R10.2; also elsewhere on the board
DVDD: C14.1, C15.1, C16.1, U1.48 (DVDD), U1.50 (DVDD); also elsewhere on the board
E_RLD: ESD17.1 (IO), R6.2, R7.1; also elsewhere on the board
GND: C1.2, C2.2, C3.2, C4.2, C5.2, C6.2, C7.2, C8.2, C9.2, C10.2, C11.2, C12.2, C13.2, C14.2, C15.2, C16.2, C17.2, ESD17.2 (GND), R2.2, R7.2, R11.2, R12.2, R13.2, R14.2, R15.2, R16.2, R17.2, R18.2, R19.2, R20.2, R40.2, U1.20 (AVSS), U1.23 (AVSS), U1.25 (VREFN), U1.31 (RESV1), U1.32 (AVSS), U1.33 (DGND), U1.38 (START), U1.41 (DAISY_IN), U1.49 (DGND), U1.51 (DGND), U1.53 (AVSS1), U1.57 (AVSS), U1.58 (AVSS); also elsewhere on the board
RLDINV: C18.2, R4.2, U1.61 (RLDINV)
RLDOUT: C18.1, R3.1, R5.1, U1.63 (RLDOUT)
RLDREF: C17.1, R1.2, R2.1, U1.60 (RLDREF)
RLD_FB: R3.2, R4.1
RLD_MID: R5.2, R6.1
SCLK_B: R8.1; also elsewhere on the board
VCAP1: C3.1, U1.28 (VCAP1); also elsewhere on the board
VCAP2: C4.1, U1.30 (VCAP2)
VCAP3: C5.1, C6.1, U1.55 (VCAP3)
VCAP4: C7.1, U1.26 (VCAP4)
VREFP: C1.1, C2.1, U1.24 (VREFP)
